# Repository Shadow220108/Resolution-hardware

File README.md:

# Resolution-hardware
## Week-1 

For week 1, I built an RC LED circuit! Where 5 LEDs light up with small delays and fade in the same way to create a cool effect!

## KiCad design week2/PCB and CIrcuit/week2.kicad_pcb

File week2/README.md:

# Resolution-hardware
## Week-2

For week 2, I built a sequence of LEDs which light up in a sequence and keep repeating to make an infinite loop
## The Circuit  

the first LED connects to the last one causing the circuit to run indefinitely.

[Demo link if gif doesnt load](https://cdn.hackclub.com/019d24c6-7a40-7489-aec7-a1c0864a2d03/final.gif)

### PCB
The PCB is designed in a heart shape with LEDs on the edge

| Schematics          |
| ------------------- |
|  |

| PCB                                     |
| --------------------------------------- |
|  |

| PS : Some PCB art      |
| ---------------------- |
|  |
|  |

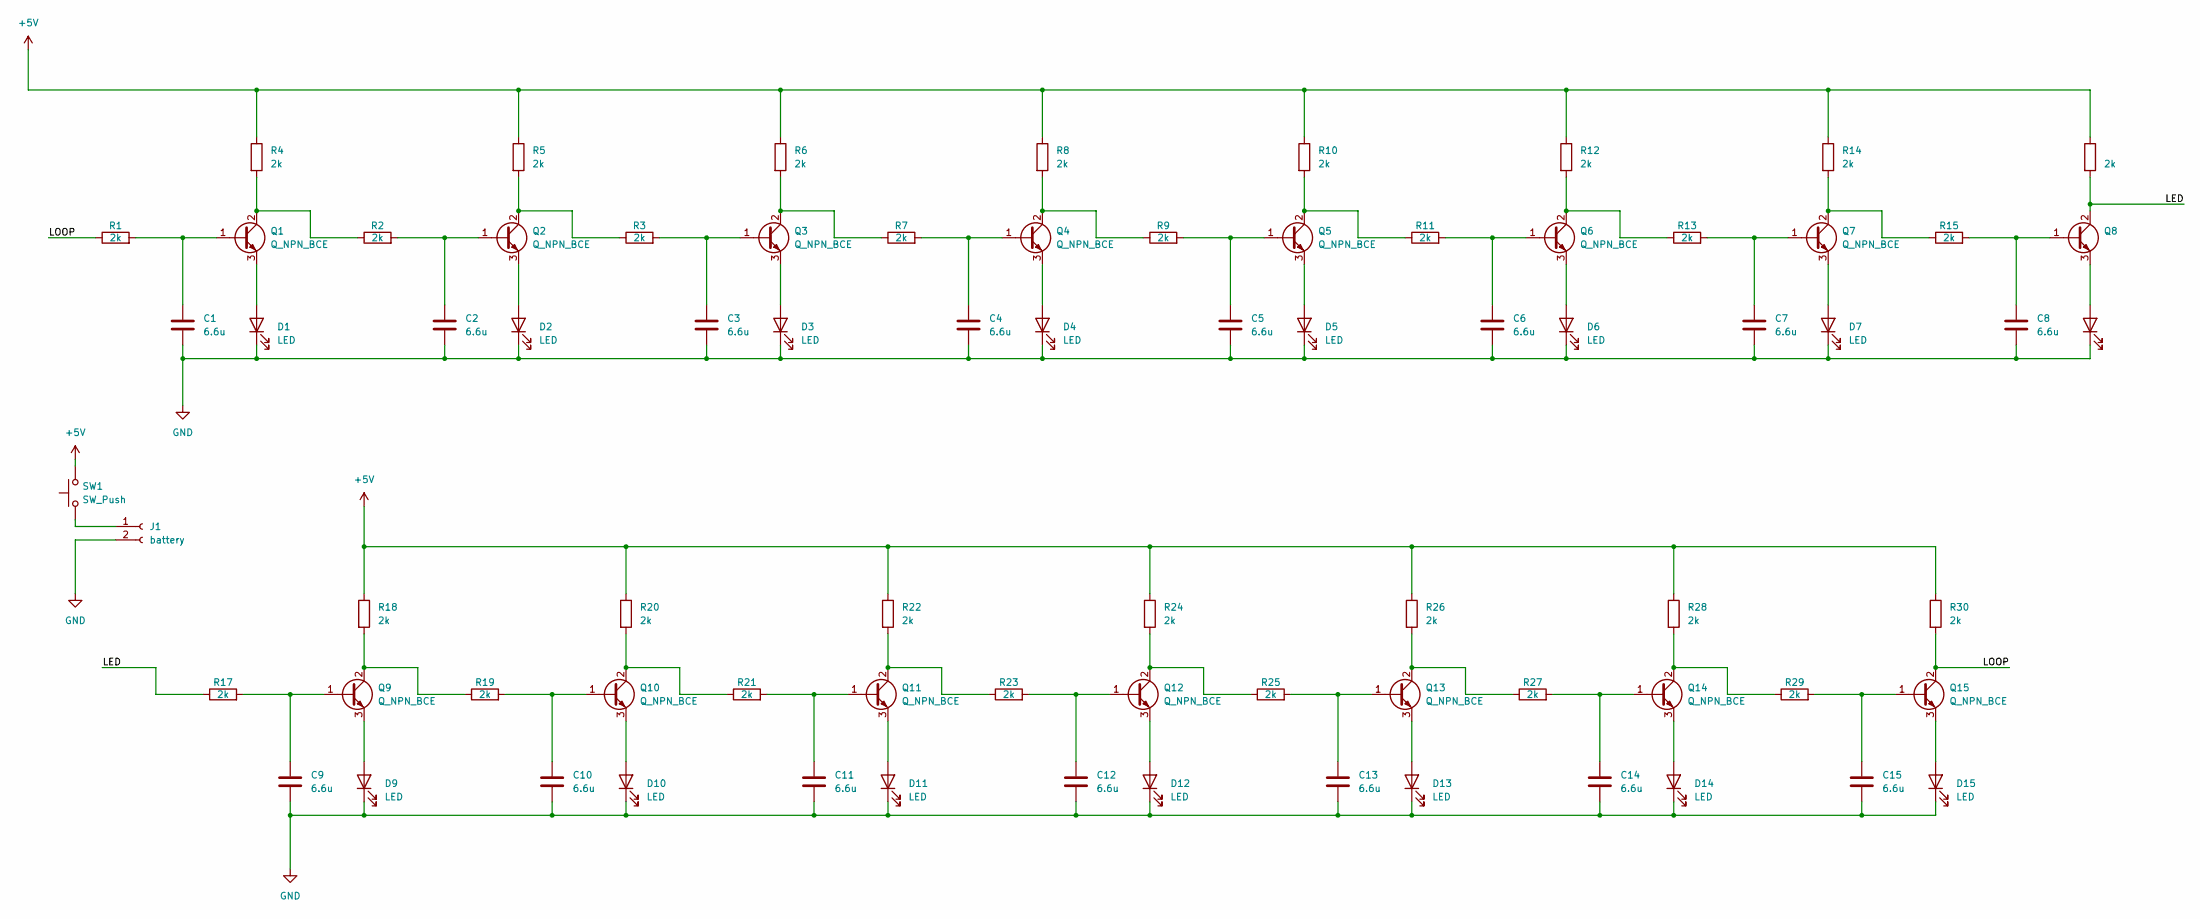
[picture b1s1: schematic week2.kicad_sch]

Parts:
C1, C2, C3, C4, C5, C6, C7, C8, C9, C10, C11, C12, C13, C14, C15: 6.6u; C_Disc_D5.0mm_W2.5mm_P5.00mm
D1, D2, D3, D4, D5, D6, D7, D8, D9, D10, D11, D12, D13, D14, D15: LED; LED_D5.0mm
J1: battery; PinHeader_1x02_P2.54mm_Vertical
Q1, Q2, Q3, Q4, Q5, Q6, Q7, Q8, Q9, Q10, Q11, Q12, Q13, Q14, Q15: Q_NPN_BCE; TO-92L_Inline_Wide
R1, R2, R3, R4, R5, R6, R7, R8, R9, R10, R11, R12, R13, R14, R15, R16, R17, R18, R19, R20, R21, R22, R23, R24, R25, R26, R27, R28, R29, R30: 2k; R_Axial_DIN0204_L3.6mm_D1.6mm_P7.62mm_Horizontal
SW1: SW_Push; SW_PUSH_6mm

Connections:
+5V: R4.1, R5.1, R6.1, R8.1, R10.1, R12.1, R14.1, R16.1, R18.1, R20.1, R22.1, R24.1, R26.1, R28.1, R30.1, SW1.2
/LED: Q8.2 (C), R16.2, R17.1
/LOOP: Q15.2 (C), R1.1, R30.2
GND: C1.2, C2.2, C3.2, C4.2, C5.2, C6.2, C7.2, C8.2, C9.2, C10.2, C11.2, C12.2, C13.2, C14.2, C15.2, D1.1 (K), D2.1 (K), D3.1 (K), D4.1 (K), D5.1 (K), D6.1 (K), D7.1 (K), D8.1 (K), D9.1 (K), D10.1 (K), D11.1 (K), D12.1 (K), D13.1 (K), D14.1 (K), D15.1 (K), J1.2
unnamed: D1.2 (A), Q1.3 (E)
unnamed: D2.2 (A), Q2.3 (E)
unnamed: D3.2 (A), Q3.3 (E)
unnamed: D4.2 (A), Q4.3 (E)
unnamed: D5.2 (A), Q5.3 (E)
unnamed: D6.2 (A), Q6.3 (E)
unnamed: D7.2 (A), Q7.3 (E)
unnamed: D8.2 (A), Q8.3 (E)
unnamed: D9.2 (A), Q9.3 (E)
unnamed: D10.2 (A), Q10.3 (E)
unnamed: D11.2 (A), Q11.3 (E)
unnamed: D12.2 (A), Q12.3 (E)
unnamed: D13.2 (A), Q13.3 (E)
unnamed: D14.2 (A), Q14.3 (E)
unnamed: D15.2 (A), Q15.3 (E)
unnamed: J1.1, SW1.1
unnamed: C1.1, Q1.1 (B), R1.2
unnamed: Q1.2 (C), R2.1, R4.2
unnamed: C2.1, Q2.1 (B), R2.2
unnamed: Q2.2 (C), R3.1, R5.2
unnamed: C3.1, Q3.1 (B), R3.2
unnamed: Q3.2 (C), R6.2, R7.1
unnamed: C4.1, Q4.1 (B), R7.2
unnamed: Q4.2 (C), R8.2, R9.1
unnamed: C5.1, Q5.1 (B), R9.2
unnamed: Q5.2 (C), R10.2, R11.1
unnamed: C6.1, Q6.1 (B), R11.2
unnamed: Q6.2 (C), R12.2, R13.1
unnamed: C7.1, Q7.1 (B), R13.2
unnamed: Q7.2 (C), R14.2, R15.1
unnamed: C8.1, Q8.1 (B), R15.2
unnamed: C9.1, Q9.1 (B), R17.2
unnamed: Q9.2 (C), R18.2, R19.1
unnamed: C10.1, Q10.1 (B), R19.2
unnamed: Q10.2 (C), R20.2, R21.1
unnamed: C11.1, Q11.1 (B), R21.2
unnamed: Q11.2 (C), R22.2, R23.1
unnamed: C12.1, Q12.1 (B), R23.2
unnamed: Q12.2 (C), R24.2, R25.1
unnamed: C13.1, Q13.1 (B), R25.2
unnamed: Q13.2 (C), R26.2, R27.1
unnamed: C14.1, Q14.1 (B), R27.2
unnamed: Q14.2 (C), R28.2, R29.1
unnamed: C15.1, Q15.1 (B), R29.2

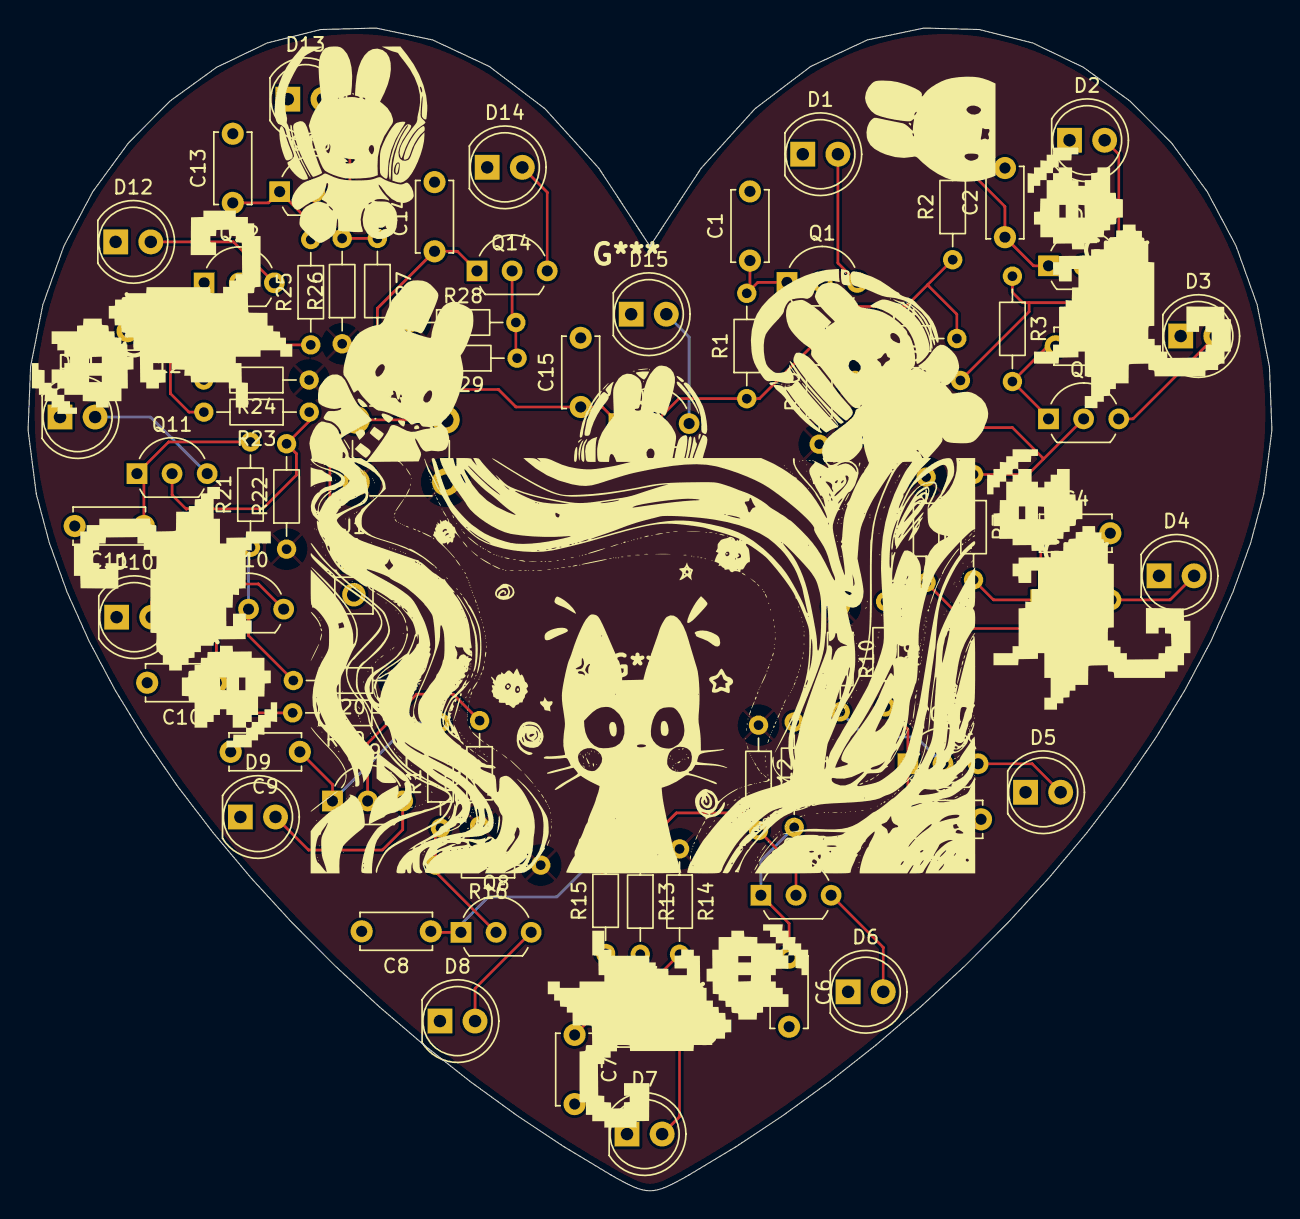
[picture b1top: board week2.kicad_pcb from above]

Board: 2 copper layers, 90.0 x 84.1 mm, 77 parts (0 on the bottom side), 48 nets.

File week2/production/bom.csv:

Designator,Footprint,Quantity,Value,LCSC Part #
"C1, C10, C11, C12, C13, C14, C15, C2, C3, C4, C5, C6, C7, C8, C9",C_Disc_D5.0mm_W2.5mm_P5.00mm,15,6.6u,
"D1, D10, D11, D12, D13, D14, D15, D2, D3, D4, D5, D6, D7, D8, D9",LED_D5.0mm,15,LED,
J1,PinHeader_1x02_P2.54mm_Vertical,1,battery,
"Q1, Q10, Q11, Q12, Q13, Q14, Q15, Q2, Q3, Q4, Q5, Q6, Q7, Q8, Q9",TO-92L_Inline_Wide,15,Q_NPN_BCE,
"R1, R10, R11, R12, R13, R14, R15, R16, R17, R18, R19, R2, R20, R21, R22, R23, R24, R25, R26, R27, R28, R29, R3, R30, R4, R5, R6, R7, R8, R9",R_Axial_DIN0204_L3.6mm_D1.6mm_P7.62mm_Horizontal,30,2k,
SW1,SW_PUSH_6mm,1,SW_Push,

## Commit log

2026-03-14 Uploading files from local repo
2026-03-25 Uploading files for 2nd week
